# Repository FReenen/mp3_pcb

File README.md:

# ANE10 PCB 2 - MP3 Speler

   This is work in progress!

A MP3 player with a ethernet interface.

## interface

   Work in progress.

## voeding

Thare a two power supplies on the board. One for het analog circuitry and
one for the part. Thes power rails are isolated. If you want to use
two separate power supplies to improve audio quality you can.

Both power supplies don't have to be regulated and support a range of 10
to 30 V.

## housing

   Work in progress.

The idea is to make a sort of rack to 'click' it in as a card,
that's why there is a weird cutout on the board.

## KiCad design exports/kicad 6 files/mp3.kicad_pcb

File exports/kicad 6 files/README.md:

# MP3 speler

Dit is een Kicad 6 project gemaakt met de nighly build.

## Kicad versie info

```txt
Application: KiCad

Version: (5.99.0-8361-gd4c36230d2), release build

Libraries:
  wxWidgets 3.0.5
  libcurl/7.71.0 OpenSSL/1.1.1g (Schannel) zlib/1.2.11 brotli/1.0.7 libidn2/2.3.0 libpsl/0.21.0 (+libidn2/2.3.0) libssh2/1.9.0 nghttp2/1.41.0

Platform: Windows 10 (build 19042), 64-bit edition, 64 bit, Little endian, wxMSW

Build Info:
  Date: Jan 12 2021 09:58:30
  wxWidgets: 3.0.5 (wchar_t,wx containers,compatible with 2.8)
  Boost: 1.73.0
  OCE: 6.9.1
  Curl: 7.71.0
  ngspice: 32
  Compiler: GCC 10.2.0 with C++ ABI 1014

Build settings:
  KICAD_SCRIPTING=ON
  KICAD_SCRIPTING_MODULES=ON
  KICAD_SCRIPTING_PYTHON3=OFF
  KICAD_SCRIPTING_WXPYTHON=ON
  KICAD_SCRIPTING_WXPYTHON_PHOENIX=OFF
  KICAD_SCRIPTING_ACTION_MENU=ON
  KICAD_USE_OCE=ON
  KICAD_SPICE=ON
```

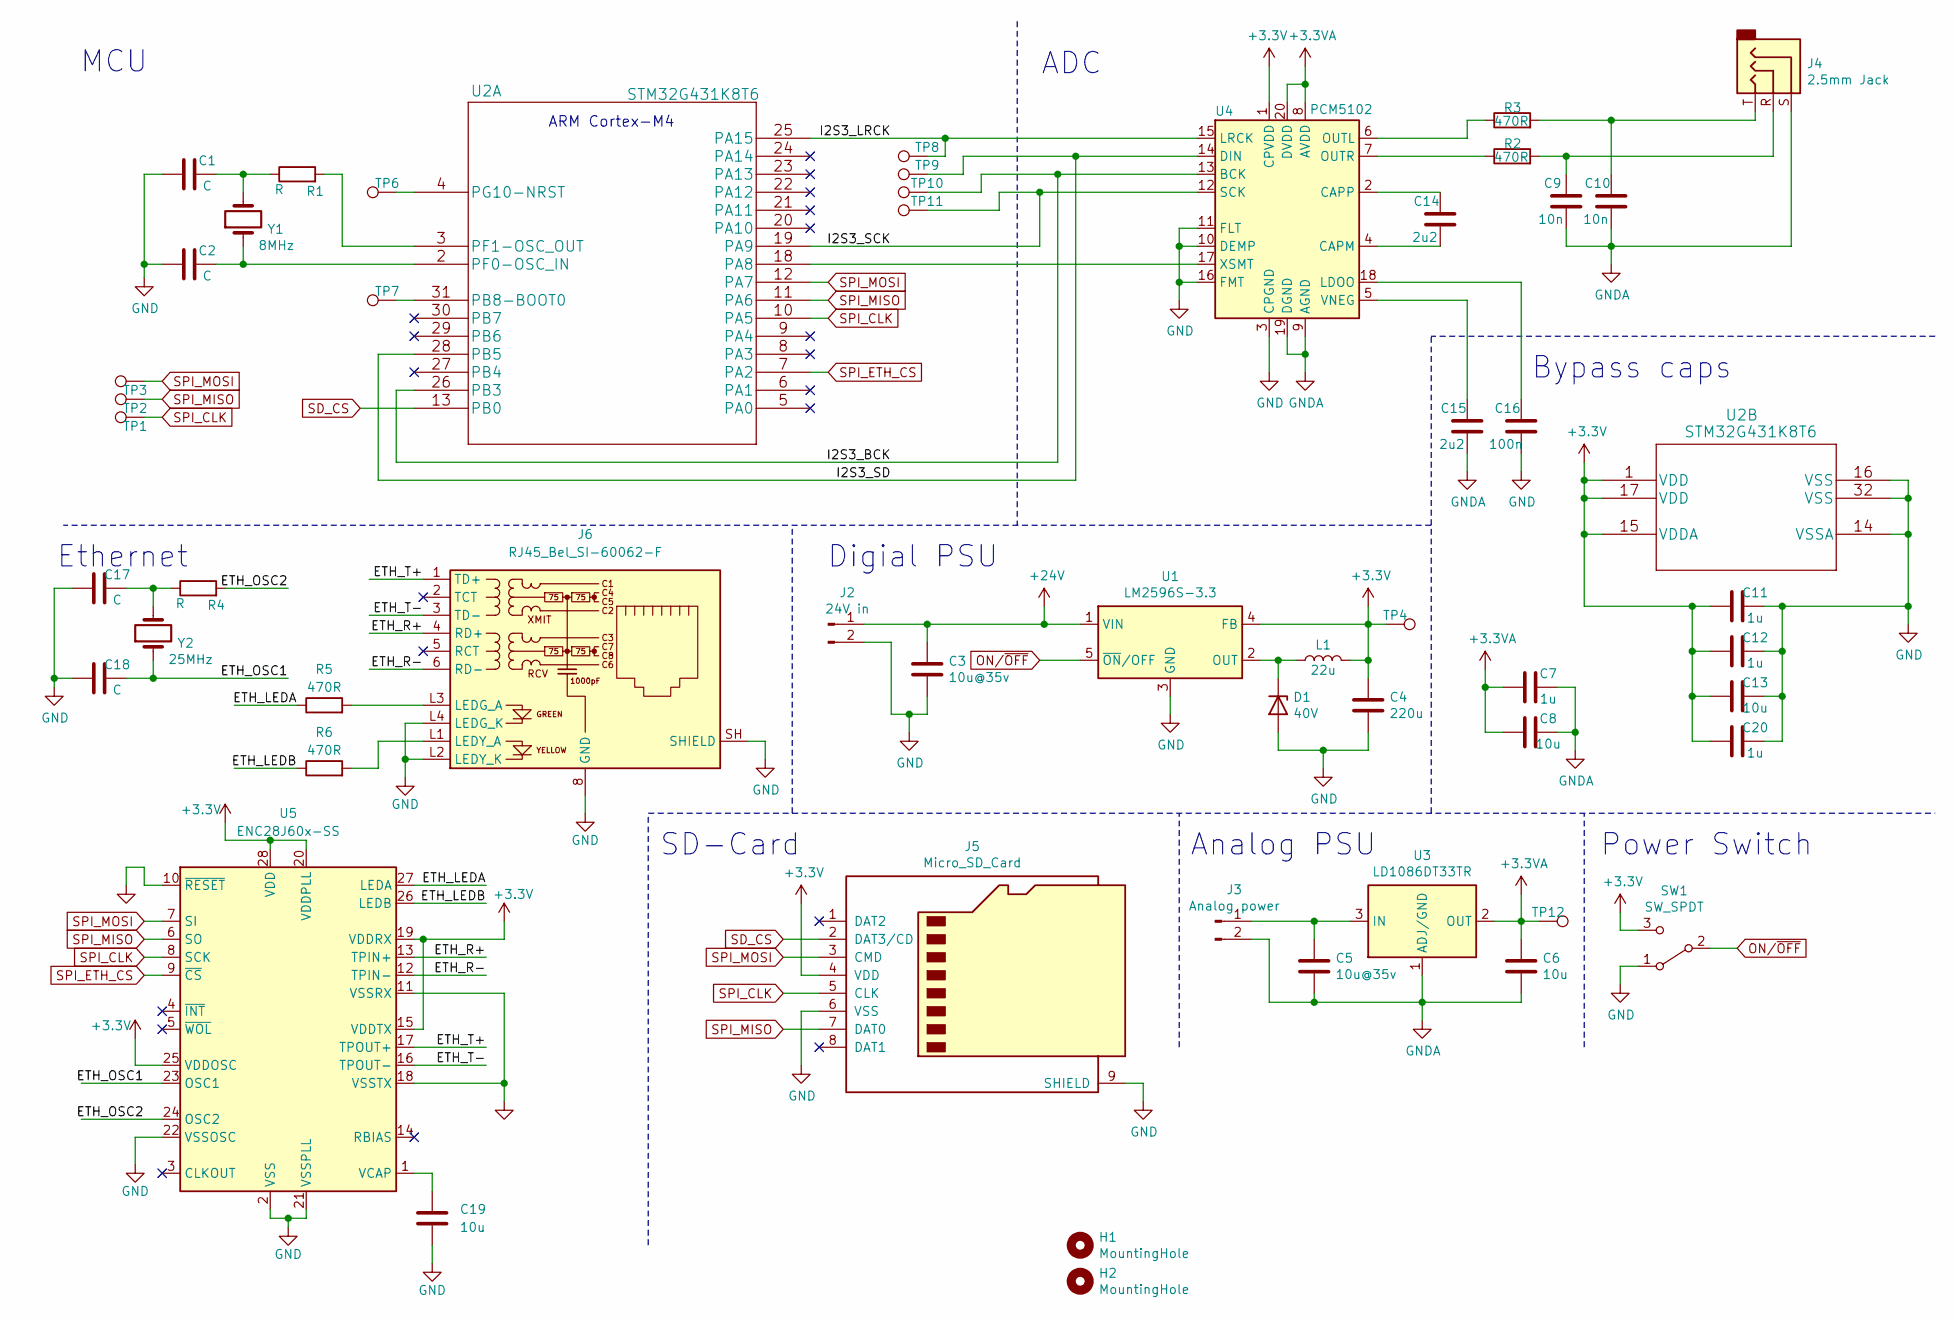
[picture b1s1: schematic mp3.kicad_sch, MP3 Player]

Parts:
C1, C2, C17, C18: C; C_0805_2012Metric
C3, C5: 10u@35v; C_1206_3216Metric
C4: 220u; C_1206_3216Metric
C6, C8, C13, C19: 10u; C_0805_2012Metric
C7, C11, C12, C20: 1u; C_0603_1608Metric
C9, C10: 10n; C_0805_2012Metric
C14, C15: 2u2; C_0805_2012Metric
C16: 100n; C_0805_2012Metric
D1: 40V; D_SOD-123F
H1, H2: MountingHole; MountingHole_3.2mm_M3
J2: 24V in; Molex_KK-254_AE-6410-02A_1x02_P2.54mm_Vertical
J3: Analog power; Molex_KK-254_AE-6410-02A_1x02_P2.54mm_Vertical
J4: 2.5mm Jack; Jack_3.5mm_CUI_SJ1-3533NG_Horizontal
J5: Micro_SD_Card; microSD_HC_Hirose_DM3D-SF
J6: RJ45_Bel_SI-60062-F
L1: 22u; L_12x12mm_H8mm
R1, R4: R; R_0805_2012Metric
R2, R3, R5, R6: 470R; R_0805_2012Metric
SW1: SW_SPDT; SW_E-Switch_EG1224_SPDT_Angled
TP1, TP2, TP3, TP4, TP6, TP7, TP8, TP9, TP10, TP11, TP12: TestPoint; TestPoint_Pad_D1.0mm
U1: LM2596S-3.3; TO-263-5_TabPin3
U2: STM32G431K8T6; LQFP-32_7x7mm_P0.8mm
U3: LD1086DT33TR; TO-252-2
U4: PCM5102; TSSOP-20_4.4x6.5mm_P0.65mm
U5: ENC28J60x-SS; SSOP-28_5.3x10.2mm_P0.65mm
Y1: 8MHz; Crystal_HC49-4H_Vertical
Y2: 25MHz; Crystal_HC49-4H_Vertical

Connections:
+3.3VA: C6.1, C7.1, C8.1, TP12.1, U3.2 (OUT), U4.8 (AVDD), U4.20 (DVDD)
+3V3: C4.1, C11.1, C12.1, C13.1, C20.1, J5.4 (VDD), L1.2, SW1.3 (C), TP4.1, U1.4 (FB), U2.1 (VDD), U2.15 (VDDA), U2.17 (VDD), U4.1 (CPVDD), U5.15 (VDDTX), U5.19 (VDDRX), U5.20 (VDDPLL), U5.25 (VDDOSC), U5.28 (VDD)
+24V: C3.1, J2.1, U1.1 (VIN)
/ETH_LEDA: R5.1, U5.27 (LEDA)
/ETH_LEDB: R6.1, U5.26 (LEDB)
/ETH_OSC1: C18.2, U5.23 (OSC1), Y2.1
/ETH_OSC2: R4.2, U5.24 (OSC2)
/ETH_R+: J6.4 (RD+), U5.13 (TPIN+)
/ETH_R-: J6.6 (RD-), U5.12 (TPIN-)
/ETH_T+: J6.1 (TD+), U5.17 (TPOUT+)
/ETH_T-: J6.3 (TD-), U5.16 (TPOUT-)
/I2S3_BCK: TP10.1, U2.26 (PB3), U4.13 (BCK)
/I2S3_LRCK: TP8.1, U2.25 (PA15), U4.15 (LRCK)
/I2S3_SCK: TP11.1, U2.19 (PA9), U4.12 (SCK)
/I2S3_SD: TP9.1, U2.28 (PB5), U4.14 (DIN)
GND: C1.1, C2.1, C3.2, C4.2, C11.2, C12.2, C13.2, C16.1, C17.1, C18.1, C19.2, C20.2, D1.2 (A), J2.2, J5.6 (VSS), J5.9 (SHIELD), J6.8 (GND), J6.L2 (LEDY_K), J6.L4 (LEDG_K), J6.SH (SHIELD), SW1.1 (A), U1.3 (GND), U2.14 (VSSA), U2.16 (VSS), U2.32 (VSS), U4.3 (CPGND), U4.10 (DEMP), U4.11 (FLT), U4.16 (FMT), U5.2 (VSS), U5.10 (~RESET), U5.11 (VSSRX), U5.18 (VSSTX), U5.21 (VSSPLL), U5.22 (VSSOSC)
GNDA: C5.2, C6.2, C7.2, C8.2, C9.1, C10.1, C15.1, J3.2, J4.S, U3.1 (ADJ/GND), U4.9 (AGND), U4.19 (DGND)
unnamed: C1.2, R1.1, Y1.2
unnamed: C2.2, U2.2 (PF0-OSC_IN), Y1.1
unnamed: C5.1, J3.1, U3.3 (IN)
unnamed: C9.2, J4.R, R2.2
unnamed: C10.2, J4.T, R3.2
unnamed: C14.1, U4.4 (CAPM)
unnamed: C14.2, U4.2 (CAPP)
unnamed: C15.2, U4.5 (VNEG)
unnamed: C16.2, U4.18 (LDOO)
unnamed: C17.2, R4.1, Y2.2
unnamed: C19.1, U5.1 (VCAP)
unnamed: D1.1 (K), L1.1, U1.2 (OUT)
unnamed: J6.L1 (LEDY_A), R6.2
unnamed: J6.L3 (LEDG_A), R5.2
unnamed: R1.2, U2.3 (PF1-OSC_OUT)
unnamed: R2.1, U4.7 (OUTR)
unnamed: R3.1, U4.6 (OUTL)
unnamed: TP6.1, U2.4 (PG10-NRST)
unnamed: TP7.1, U2.31 (PB8-BOOT0)
unnamed: U2.18 (PA8), U4.17 (XSMT)
ON/~OFF: SW1.2 (B), U1.5 (~ON~/OFF)
SD_CS: J5.2 (DAT3/CD), U2.13 (PB0)
SPI_CLK: J5.5 (CLK), TP1.1, U2.10 (PA5), U5.8 (SCK)
SPI_ETH_CS: U2.7 (PA2), U5.9 (~CS)
SPI_MISO: J5.7 (DAT0), TP2.1, U2.11 (PA6), U5.6 (SO)
SPI_MOSI: J5.3 (CMD), TP3.1, U2.12 (PA7), U5.7 (SI)
no_connect_45: J5.1 (DAT2)
no_connect_46: J5.8 (DAT1)
no_connect_47: J6.2 (TCT)
no_connect_48: J6.5 (RCT)
no_connect_49: U2.20 (PA10)
no_connect_50: U2.21 (PA11)
no_connect_51: U2.22 (PA12)
no_connect_52: U2.23 (PA13)
no_connect_53: U2.24 (PA14)
no_connect_54: U2.27 (PB4)
no_connect_55: U2.29 (PB6)
no_connect_56: U2.30 (PB7)
no_connect_57: U2.5 (PA0)
no_connect_58: U2.6 (PA1)
no_connect_59: U2.8 (PA3)
no_connect_60: U2.9 (PA4)
no_connect_61: U5.3 (CLKOUT)
no_connect_62: U5.4 (~INT)
no_connect_63: U5.5 (~WOL)
no_connect_64: J6.7 (NC)

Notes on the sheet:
MCU
Ethernet
ARM Cortex-M4
SD-Card
Digial PSU
ADC
Analog PSU
Bypass caps
Power Switch

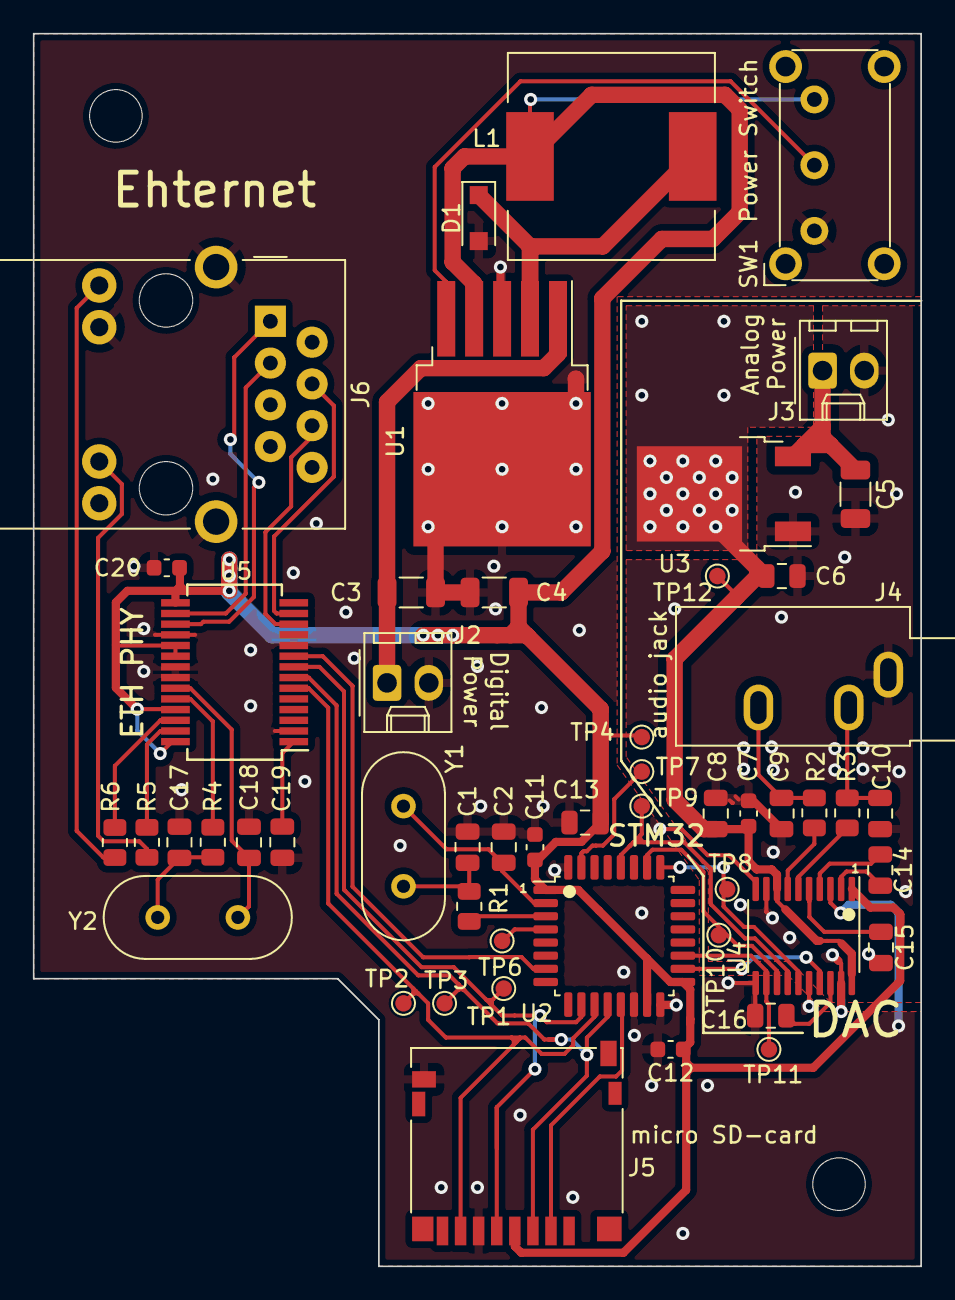
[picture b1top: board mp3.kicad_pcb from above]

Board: 2 copper layers, 54.0 x 75.0 mm, 54 parts (0 on the bottom side), 43 nets.

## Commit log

2021-01-06 V0.1
2021-01-08 v0.2
2021-01-14 cleanup
